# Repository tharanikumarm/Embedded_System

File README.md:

# 🚀 Embedded Systems Learning – Embedded C

Welcome to my embedded systems learning repository!  
This repo serves as my personal learning log, project space, and portfolio for exploring **Embedded C programming**.

---

## 📚 About This Repository

This repository includes:

- ✍️ **Practice programs** in Embedded C      
- 🧠 **Code snippets and notes** from my learning journey  

I am currently learning embedded systems with limited time (about 1 hour daily), so this repository reflects my real-time progress. It will evolve as I grow in knowledge and experience.

---

Each folder contains:
- Source code
- README or comments describing functionality

---

## 🎯 Goals

- Understand the fundamentals of Embedded C
- Develop hands-on experience with STM32CubeIDE and STM32 microcontrollers
- Create a personal reference and project showcase

---

## 🛠 Tools & Platforms

- Language: **Embedded C**
- IDE: **STM32CubeIDE**
- Microcontroller: **STM32 Blue Pill / Nucleo Boards**
- Tools: STM32 HAL drivers, STM32CubeMX, Proteus (for simulations)

---

## 🧩 Notes

- Some code might be messy, incomplete, or a work-in-progress.  
- I’m constantly learning — **feedback, suggestions, and corrections are always welcome!**  
  > Feel free to open issues or pull requests if you spot any errors or have improvements!

---

## 📬 Contact

If you're also learning embedded systems or want to collaborate, feel free to reach out:

- 🌐 LinkedIn: https://www.linkedin.com/in/tharanikumarm/

---

## 💡 License

This repository is for educational purposes. You're welcome to fork, use, and improve the content with proper attribution.

---

⭐ If you find this useful, consider giving the repo a star to support my learning journey!

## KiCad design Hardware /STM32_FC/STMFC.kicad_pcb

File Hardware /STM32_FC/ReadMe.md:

# ✈️ STM32 Based Flight Controller (Hardware Design)

This project is a custom **STM32-based flight controller PCB** designed completely in **KiCad**.  
The goal of this project was to understand how flight controller hardware is built from scratch .

---

## 🔧 Project Overview

This is a hardware-focused flight controller design that includes:

- STM32 microcontroller-based control unit  
- Power supply and buck converter section  
- USB interface for communication  
- UART and I2C connectivity  
- SWD programming/debugging interface  
- Status and power LEDs  
- Compact 4 layer PCB layout    

Designed fully in **KiCad** from schematic → PCB .

---

## 🧠 What I Learned

- STM32 hardware design basics  
- PCB routing and layout practices  
- Power and signal routing concepts  
- Decoupling and grounding techniques  
- KiCad workflow (schematic to PCB)   

---

## 🛠 Tools Used

- **KiCad** – Schematic & PCB design  
- **STM32 CubeMX** – Main controller  
- **Embedded hardware design concepts**
  
---

## 🎯 Future Improvements

- Sensor integration (IMU, Gyro, Accelerometer)  
- Flight control firmware development  
- PID stabilization testing  
- Full drone integration

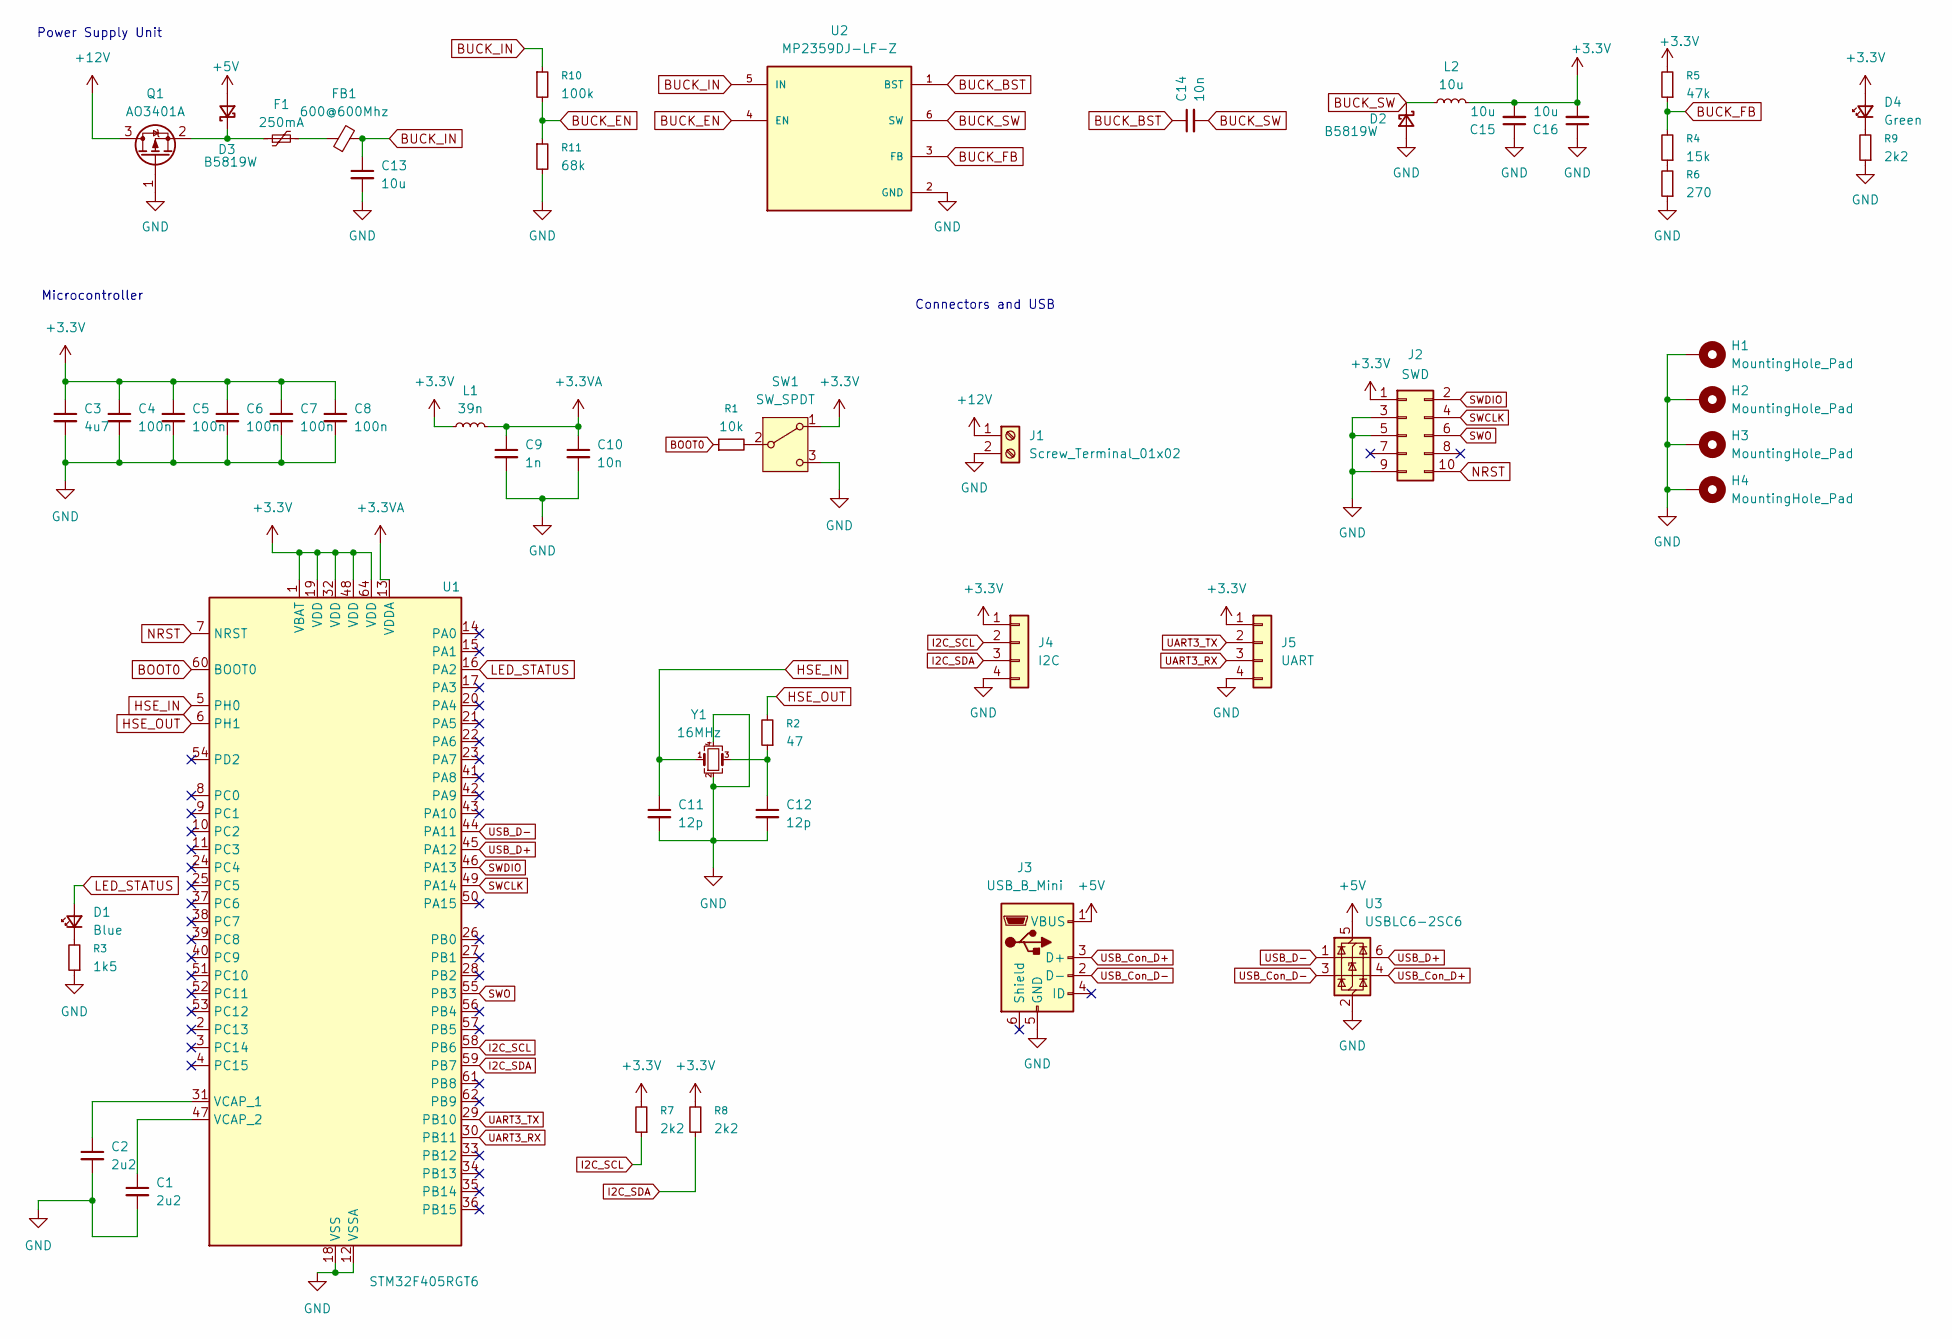
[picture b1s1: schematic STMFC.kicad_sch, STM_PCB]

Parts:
C1, C2: 2u2; C_0603_1608Metric
C3: 4u7; C_0603_1608Metric
C4, C5, C6, C7, C8: 100n; C_0402_1005Metric
C9: 1n; C_0402_1005Metric
C10: 10n; C_0402_1005Metric
C11, C12: 12p; C_0402_1005Metric
C13, C15, C16: 10u; C_1206_3216Metric
C14: 10n; C_0603_1608Metric
D1: Blue; LED_0603_1608Metric
D2, D3: B5819W; D_SOD-123
D4: Green; LED_0603_1608Metric
F1: 250mA; Fuse_1206_3216Metric
FB1: 600@600Mhz; L_0805_2012Metric
H1, H2, H3, H4: MountingHole_Pad; MountingHole_4.3mm_M4_Pad_Via
J1: Screw_Terminal_01x02; TerminalBlock_Phoenix_PT-1,5-2-3.5-H_1x02_P3.50mm_Horizontal
J2: SWD; PinHeader_2x05_P1.27mm_Vertical_SMD
J3: USB_B_Mini; USB_Mini-B_Lumberg_2486_01_Horizontal
J4: I2C; Molex_PicoBlade_53048-0410_1x04_P1.25mm_Horizontal
J5: UART; Molex_PicoBlade_53048-0410_1x04_P1.25mm_Horizontal
L1: 39n; L_0402_1005Metric
L2: 10u; L_Sunlord_MWSA0518S
Q1: AO3401A; SOT-23
R1: 10k; R_0402_1005Metric
R2: 47; R_0402_1005Metric
R3: 1k5; R_0603_1608Metric
R4: 15k; R_0603_1608Metric
R5: 47k; R_0603_1608Metric
R6: 270; R_0603_1608Metric
R7, R8: 2k2; R_0402_1005Metric
R9: 2k2; R_0603_1608Metric
R10: 100k; R_0603_1608Metric
R11: 68k; R_0603_1608Metric
SW1: SW_SPDT; SW_SPDT_PCM12
U1: STM32F405RGT6; LQFP-64_10x10mm_P0.5mm
U2: MP2359DJ-LF-Z; SOT95P280X100-6N; PARTREV 1.21
U3: USBLC6-2SC6; SOT-23-6
Y1: 16MHz; Crystal_SMD_3225-4Pin_3.2x2.5mm

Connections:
+3.3V: C3.1, C4.1, C5.1, C6.1, C7.1, C8.1, C15.2, C16.2, D4.2 (A), J2.1, J4.1, J5.1, L1.1, L2.2, R5.2, R7.2, R8.2, SW1.1 (A), U1.1 (VBAT), U1.19 (VDD), U1.32 (VDD), U1.48 (VDD), U1.64 (VDD)
+3.3VA: C9.1, C10.1, L1.2, U1.13 (VDDA)
+5V: D3.2 (A), J3.1 (VBUS), U3.5 (VBUS)
+12V: J1.1, Q1.3 (D)
BOOT0: R1.1, U1.60 (BOOT0)
BUCK_BST: C14.1, U2.1 (BST)
BUCK_EN: R10.2, R11.1, U2.4 (EN)
BUCK_FB: R4.2, R5.1, U2.3 (FB)
BUCK_IN: C13.1, FB1.2, R10.1, U2.5 (IN)
BUCK_SW: C14.2, D2.1 (K), L2.1, U2.6 (SW)
GND: C1.2, C2.2, C3.2, C4.2, C5.2, C6.2, C7.2, C8.2, C9.2, C10.2, C11.2, C12.2, C13.2, C15.1, C16.1, D2.2 (A), H1.1, H2.1, H3.1, H4.1, J1.2, J2.3, J2.5, J2.9, J3.5 (GND), J4.4, J5.4, Q1.1 (G), R3.1, R6.1, R9.1, R11.2, SW1.3 (C), U1.12 (VSSA), U1.18 (VSS), U1.63 (VSS), U2.2 (GND), U3.2 (GND), Y1.2, Y1.4
HSE_IN: C11.1, U1.5 (PH0), Y1.1
HSE_OUT: R2.2, U1.6 (PH1)
I2C_SCL: J4.2, R7.1, U1.58 (PB6)
I2C_SDA: J4.3, R8.1, U1.59 (PB7)
LED_STATUS: D1.2 (A), U1.16 (PA2)
NRST: J2.10, U1.7 (NRST)
unnamed: C12.1, R2.1, Y1.3
unnamed: D1.1 (K), R3.2
unnamed: D3.1 (K), F1.1, Q1.2 (S)
unnamed: D4.1 (K), R9.2
unnamed: F1.2, FB1.1
unnamed: R4.1, R6.2
unnamed: R1.2, SW1.2 (B)
unnamed: C2.1, U1.31 (VCAP_1)
unnamed: C1.1, U1.47 (VCAP_2)
SWCLK: J2.4, U1.49 (PA14)
SWDIO: J2.2, U1.46 (PA13)
SWO: J2.6, U1.55 (PB3)
UART3_RX: J5.3, U1.30 (PB11)
UART3_TX: J5.2, U1.29 (PB10)
USB_Con_D+: J3.3 (D+), U3.4 (I/O2)
USB_Con_D-: J3.2 (D-), U3.3 (I/O2)
USB_D+: U1.45 (PA12), U3.6 (I/O1)
USB_D-: U1.44 (PA11), U3.1 (I/O1)

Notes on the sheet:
Power Supply Unit
Microcontroller
Connectors and USB

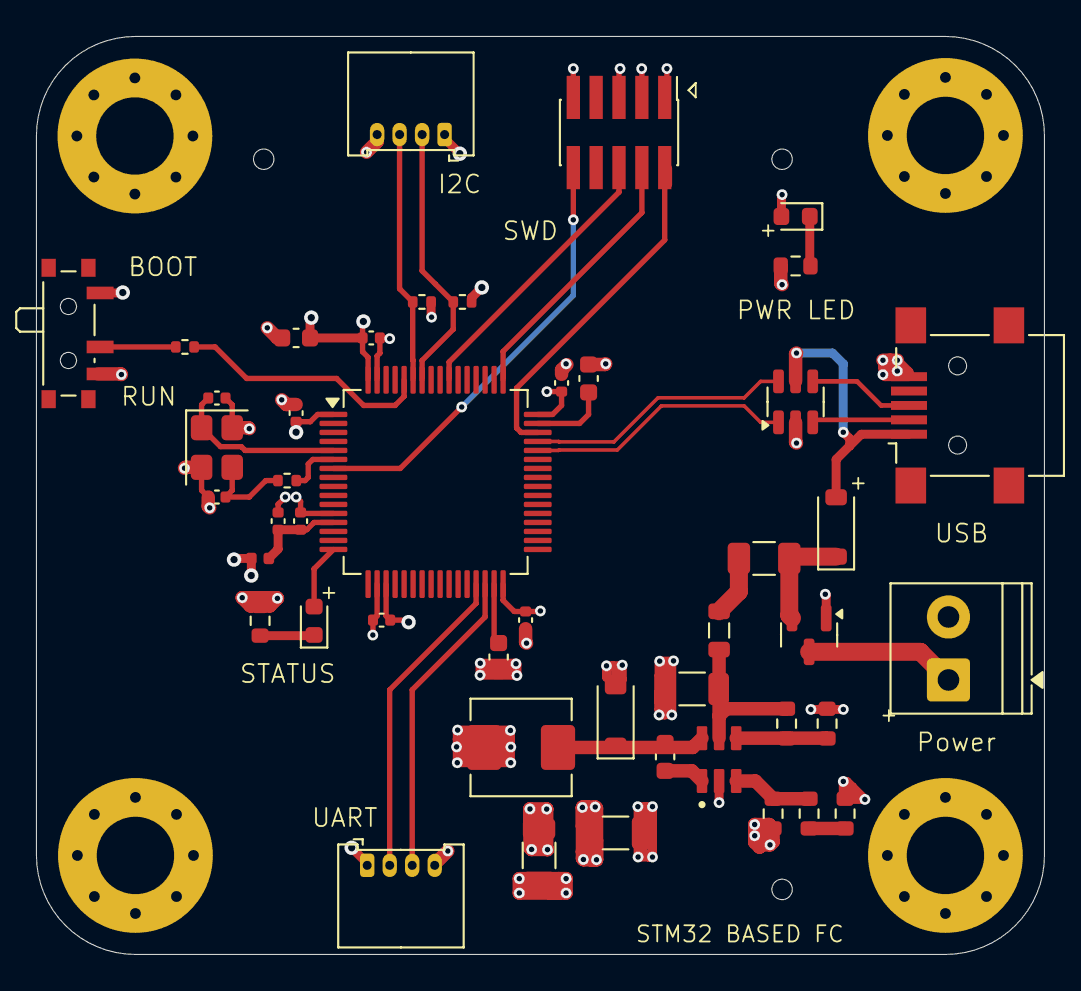
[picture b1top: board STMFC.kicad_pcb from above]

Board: 4 copper layers, 56.0 x 51.0 mm, 50 parts (0 on the bottom side), 35 nets.

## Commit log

2025-07-09 Update README.md
    not brief idea but first idea.
2025-07-10 Create programming Language.txt
    basic of the programming language
2025-12-01 Create GPIO_Driver
2026-01-06 Delete Driver_Development/GPIO_Driver
    Because this is empty file
2026-02-09 Create Hardware
    File creation
2026-02-09 Create hardware
    Hardware designs
2026-02-09 Create STM32_FC
    folder created
2026-02-09 STM32_FC
2026-02-09 Create stm32_FC
2026-02-09 Create therala
2026-02-11 Revise ReadMe for STM32 Flight Controller
    Updated project description and removed redundant details.
